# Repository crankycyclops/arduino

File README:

To install dependencies on Ubuntu 20.04:

sudo apt-get install libdevice-serialport-perl libyaml-perl

Download the Arduino IDE for your architecture here:
https://www.arduino.cc/en/software

Extract the archive:
cd /usr/local && sudo tar -xvf arduino-1.x.xx-arch.tar.xz

Symlink to the versioned directory where the IDE was installed:
sudo ln -s /usr/local/arduino-1.x.xx /usr/local/arduino

Clone the Arduino makefile repo from https://github.com/sudar/Arduino-Makefile:
cd /usr/local/arduino && sudo git clone git@github.com:sudar/Arduino-Makefile.git

Create a directory where we can store any required third party libraries:
sudo mkdir /usr/local/arduino-libraries

You can read more about this makefile I'm using here:
https://hardwarefun.com/tutorials/compiling-arduino-sketches-using-makefile

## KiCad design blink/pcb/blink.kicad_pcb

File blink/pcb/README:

This is a KiCAD project.
See: https://kicad.org/

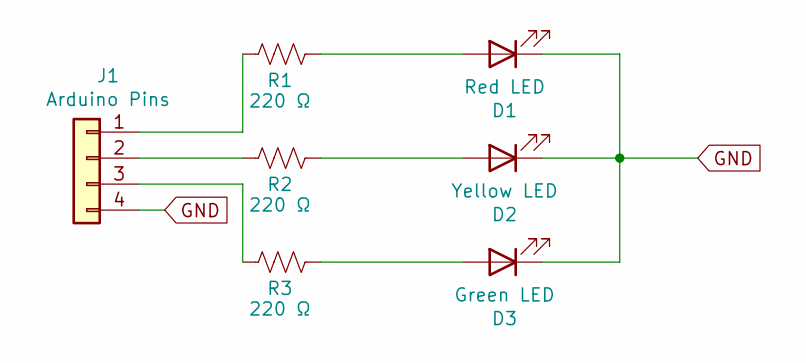
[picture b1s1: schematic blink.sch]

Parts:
D1: Red LED; LED_D3.0mm
D2: Yellow LED; LED_D3.0mm
D3: Green LED; LED_D3.0mm
J1: Arduino Pins; PinSocket_1x04_P2.54mm_Vertical
R1, R2, R3: 220 Ω; R_Axial_DIN0414_L11.9mm_D4.5mm_P15.24mm_Horizontal

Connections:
GND: D1.1 (K), D2.1 (K), D3.1 (K), J1.4
unnamed: D1.2 (A), R1.2
unnamed: D2.2 (A), R2.2
unnamed: D3.2 (A), R3.2
unnamed: J1.1, R1.1
unnamed: J1.2, R2.1
unnamed: J1.3, R3.1

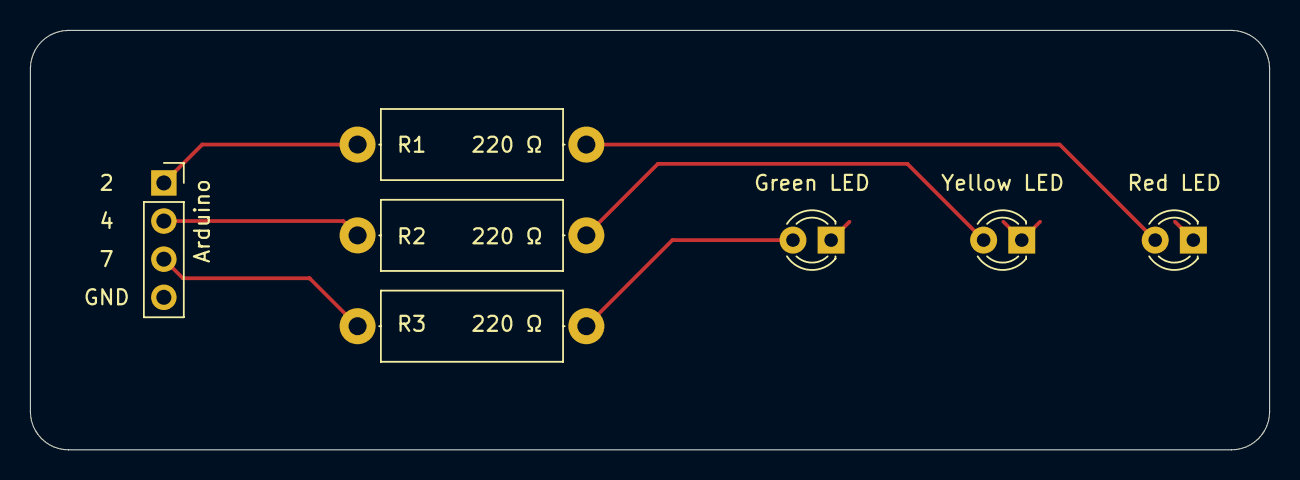
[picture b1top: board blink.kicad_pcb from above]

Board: 2 copper layers, 82.6 x 27.9 mm, 7 parts (0 on the bottom side), 7 nets.

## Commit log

2015-02-23 adding my first alarm clock project
2015-02-23 updated readmes
2015-02-23 removed old test code I left by accident :)
2015-02-23 some refactoring and optimizing for size
2015-02-24 implemented mode switching
2015-02-24 moved a line of code to a more logical location
2015-02-24 refactored, and now syncing with RTC every 4 hours
2015-03-04 added a schematic and adjusted default lcd brightness
2015-03-05 began updating schematic (but still have to add pull-down resistors to new buttons) and updated alarm.h to recognize the new buttons
2015-03-06 implemented set time mode
2015-03-06 implemented blinking time parts when setting time
2015-03-06 added ability to hide date in printTime (will be useful for setting the alarm)
2015-03-07 generalized prompt methods, added a utility module, refactored some code and implemented the setting of the date (still buggy)
2015-03-08 fixed date setting bug
2015-03-08 removed redundant code (functionality already in Time library)
2015-03-14 began implementing the alarm
2015-03-14 implemented RTC, but writing to it doesn't work properly yet
2015-03-14 fixed RTC write issue by using time_t directly
2021-02-19 updated Makefiles and instructions for setting up the build environment
2021-02-19 removed stale CREDITS file that was no longer accurate
2021-02-19 cleaned up Makefile for alarm project
2021-02-19 added instructions for uploading image
2021-02-19 added obligatory blink program
2021-02-19 modified blink to create a rolling pattern of lights
2021-02-26 reconstructed schematic for Alarm project and added schematic and PCB files for Blink project
